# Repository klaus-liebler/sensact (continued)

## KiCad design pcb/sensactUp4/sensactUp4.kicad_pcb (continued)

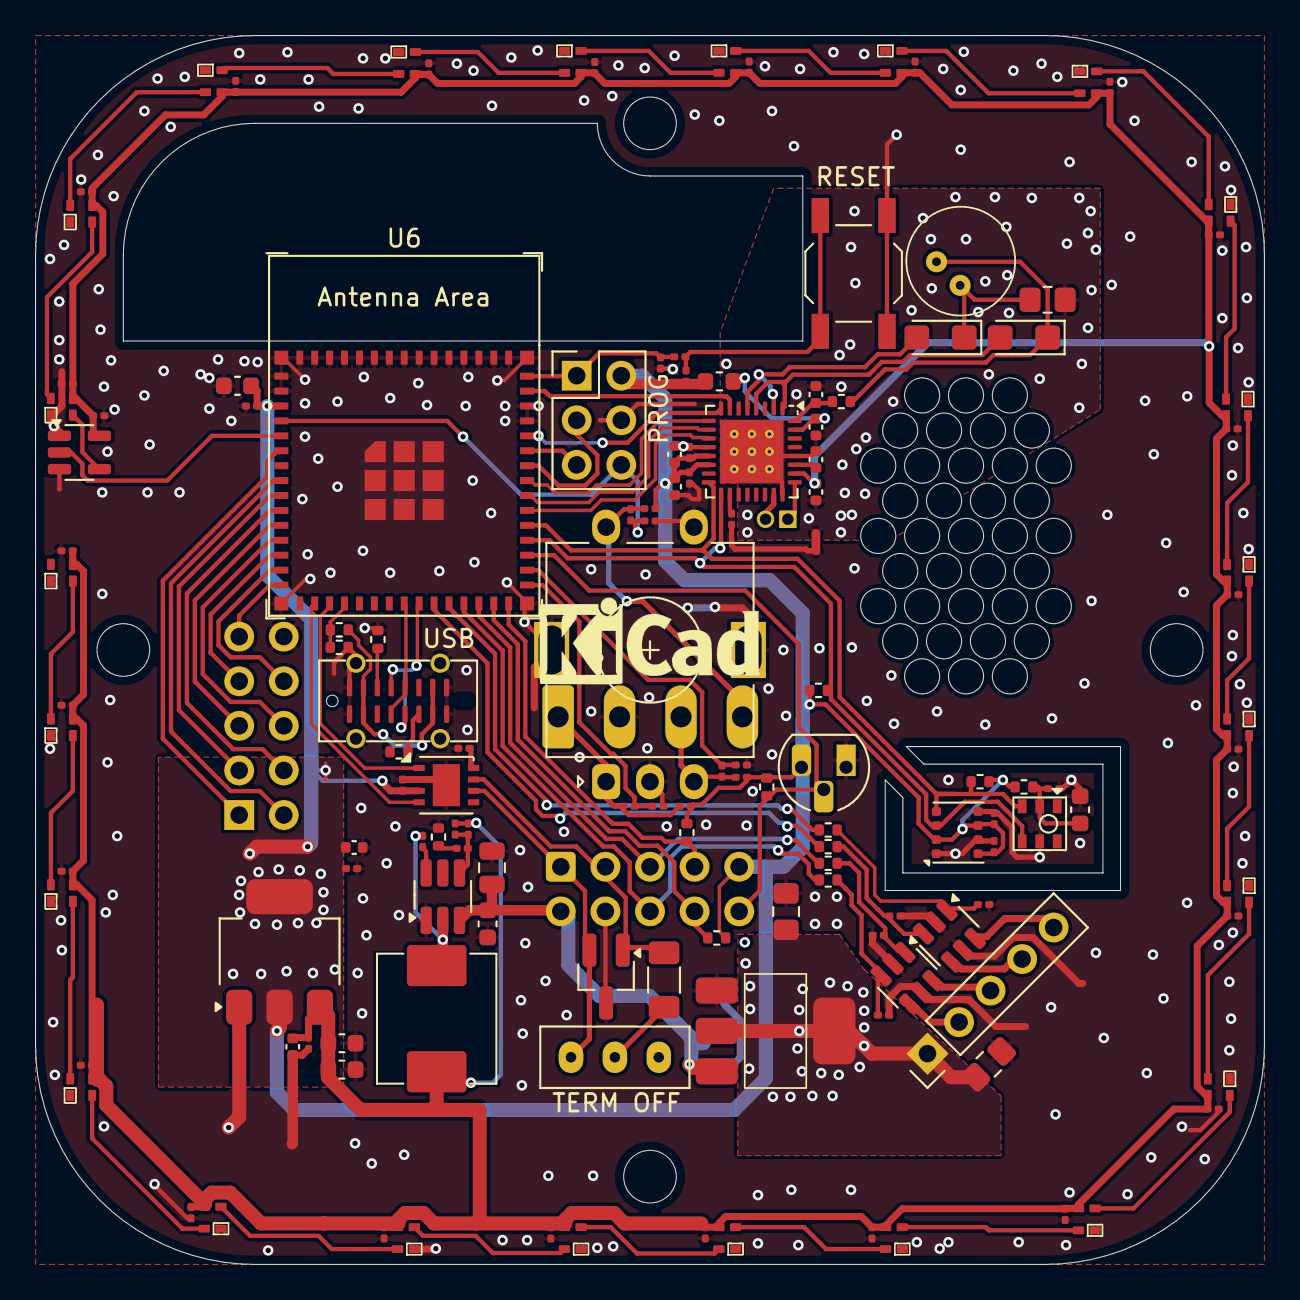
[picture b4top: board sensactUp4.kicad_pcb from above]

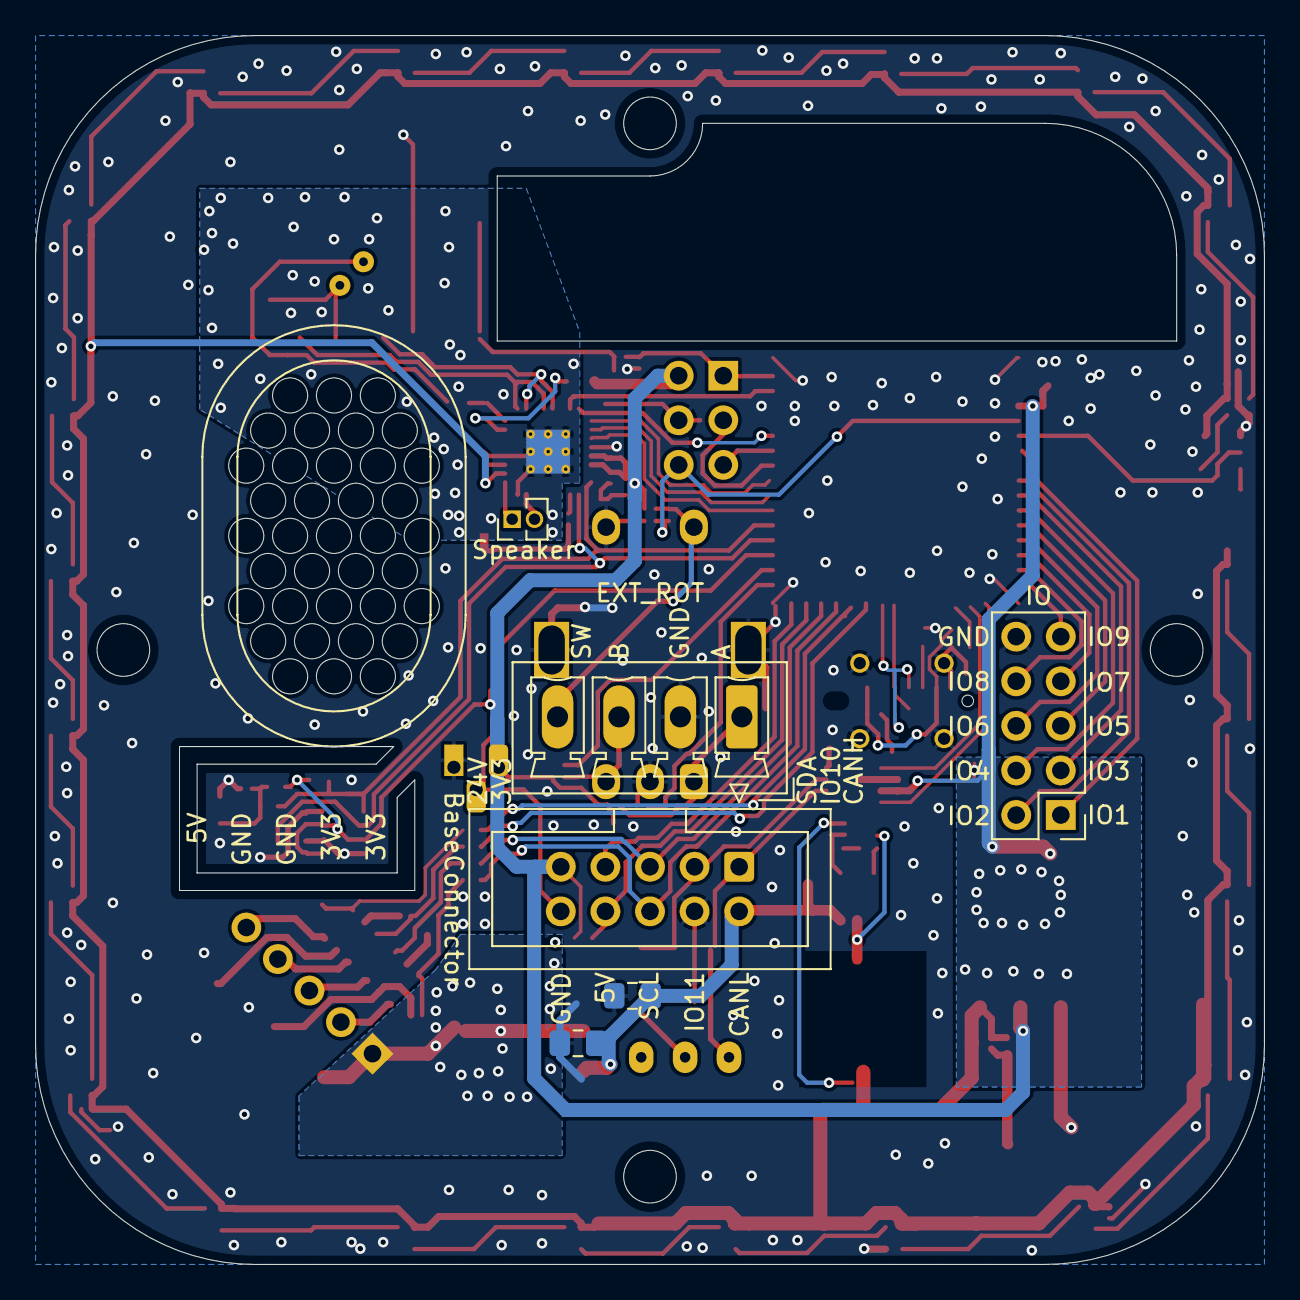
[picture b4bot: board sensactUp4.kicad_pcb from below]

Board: 2 copper layers, 70.0 x 70.0 mm, 147 parts (7 on the bottom side), 99 nets.

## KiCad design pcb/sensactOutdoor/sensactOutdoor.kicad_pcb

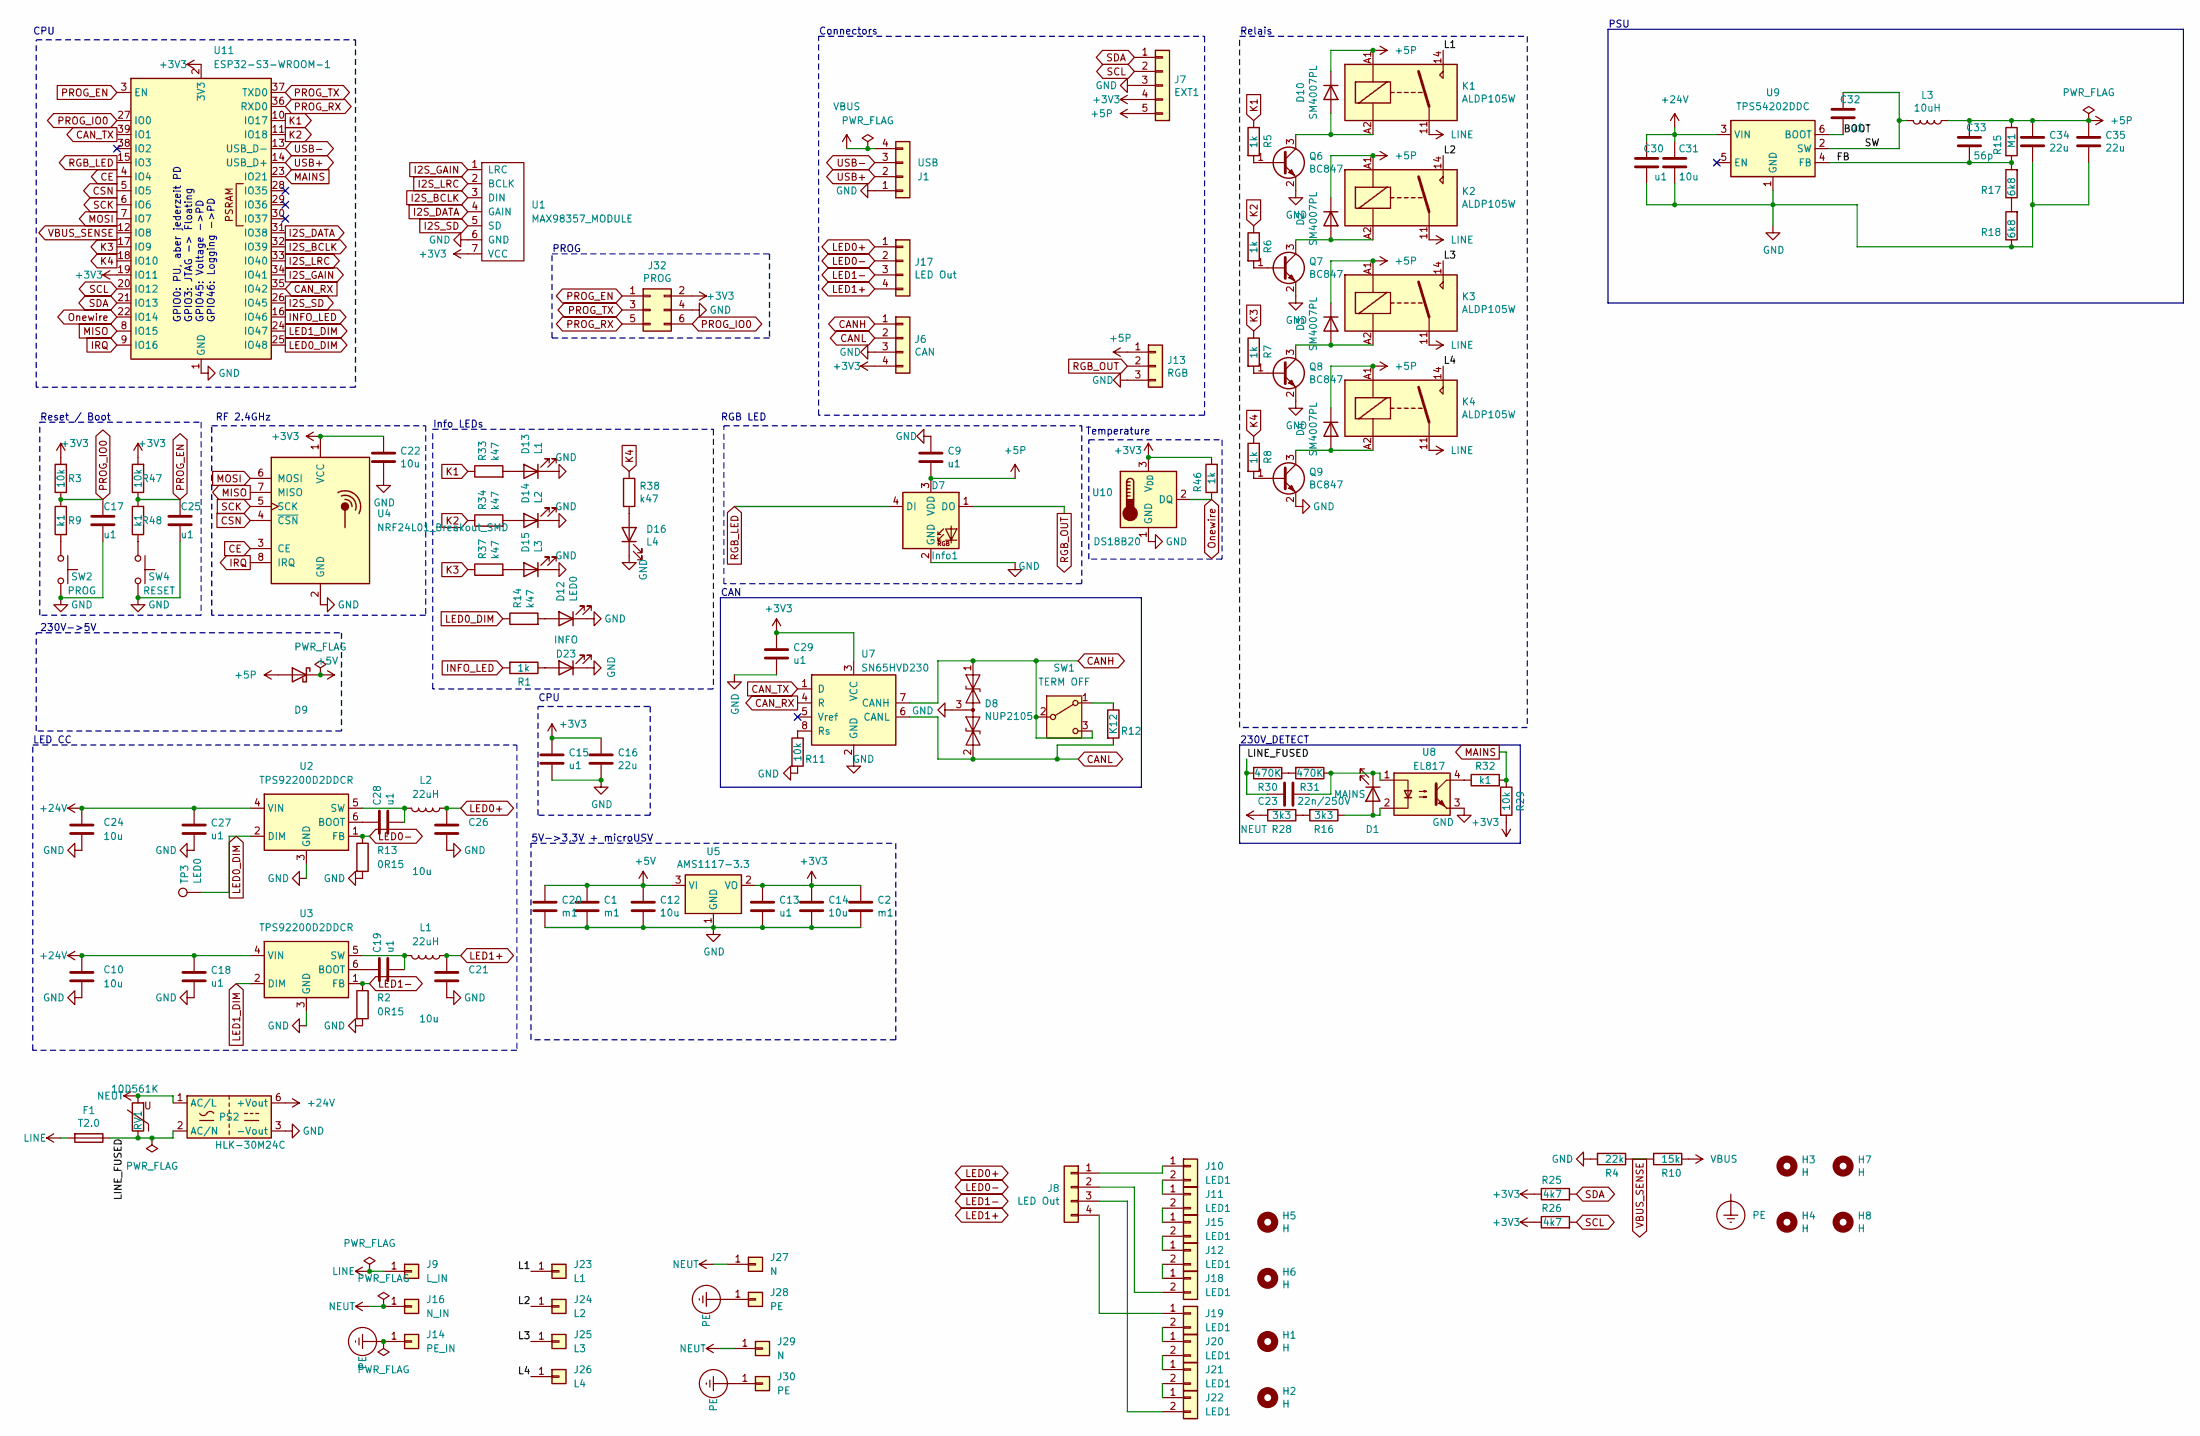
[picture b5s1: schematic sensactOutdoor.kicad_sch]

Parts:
C1, C2, C20: m1; C_1206_3216Metric; JLCPCB C15008
C9, C13, C17, C18, C19, C25, C27, C28, C30, C32: u1; C_0805_2012Metric_Pad1.18x1.45mm_HandSolder
C10, C21, C24, C26, C31: 10u; C_1206_3216Metric_Pad1.33x1.80mm_HandSolder
C12: 10u; C_0805_2012Metric_Pad1.18x1.45mm_HandSolder; JLCPCB C19702
C14, C22: 10u; C_0805_2012Metric_Pad1.18x1.45mm_HandSolder
C15: u1; C_0805_2012Metric_Pad1.18x1.45mm_HandSolder; JLCPCB C1525
C16: 22u; C_0805_2012Metric_Pad1.18x1.45mm_HandSolder; JLCPCB C59461
C23: 22n/250V; C_Rect_L11.0mm_W5.1mm_P10.00mm_MKT
C29: u1; C_0805_2012Metric; MPN GRM033R61A104KE15D
C33: 56p; C_0805_2012Metric_Pad1.18x1.45mm_HandSolder
C34, C35: 22u; C_0805_2012Metric_Pad1.18x1.45mm_HandSolder
D1: MAINS; LED_0805_2012Metric_Pad1.15x1.40mm_HandSolder
D2, D3, D4, D10: SM4007PL; D_SOD-123_handsolder; JLCPCB C64898
D7: Info1; LED_D5.0mm-4_RGB_Staggered_Pins
D8: NUP2105; SOT-23_Handsoldering; MPN NUP2105L
D9: 1N5819WS; D_SMA_Handsoldering
D12: LED0; LED_0805_2012Metric_Pad1.15x1.40mm_HandSolder; JLCPCB C2286
D13: L1; LED_0805_2012Metric_Pad1.15x1.40mm_HandSolder; JLCPCB C2286
D14: L2; LED_0805_2012Metric_Pad1.15x1.40mm_HandSolder; JLCPCB C2286
D15: L3; LED_0805_2012Metric_Pad1.15x1.40mm_HandSolder; JLCPCB C2286
D16: L4; LED_0805_2012Metric_Pad1.15x1.40mm_HandSolder; JLCPCB C2286
D23: INFO; LED_0805_2012Metric_Pad1.15x1.40mm_HandSolder
F1: T2.0; Fuse_Littelfuse_372_D8.50mm
H1, H2, H3, H4, H5, H6, H7, H8: H; MountingHole_3.2mm_M3
J1: USB; PinHeader_1x04_P2.54mm_Vertical
J6: CAN; PhoenixContact_MCV_1,5_4-G-3.5_1x04_P3.50mm_Vertical
J7: EXT1; JST_XH_B5B-XH-A_1x05_P2.50mm_Vertical
J8: LED Out; ÖLFLEX 4x1mm2
J9: L_IN; Flachstecker gewinkelt 4,8 oder 6,35mm
J10, J11, J12, J15, J18, J19, J20, J21, J22: LED1; JST_XH_B2B-XH-A_1x02_P2.50mm_Vertical
J13: RGB; PinHeader_1x03_P2.54mm_Vertical
J14: PE_IN; Flachstecker gewinkelt 4,8 oder 6,35mm
J16: N_IN; Flachstecker gewinkelt 4,8 oder 6,35mm
J17: LED Out; PhoenixContact_MCV_1,5_4-G-3.5_1x04_P3.50mm_Vertical
J23: L1; Flachstecker gewinkelt 4,8 oder 6,35mm
J24: L2; Flachstecker gewinkelt 4,8 oder 6,35mm
J25: L3; Flachstecker gewinkelt 4,8 oder 6,35mm
J26: L4; Flachstecker gewinkelt 4,8 oder 6,35mm
J27, J29: N; Flachstecker gewinkelt 4,8 oder 6,35mm
J28, J30: PE; Flachstecker gewinkelt 4,8 oder 6,35mm
J32: PROG; PinHeader_2x03_P2.54mm_Vertical
K1, K2, K3, K4: ALDP105W; RELAY_ALDP105W
L1, L2: 22uH; L_0630; JLCPCB C408455
L3: 10uH; L_0630
PS2: HLK-30M24C; Converter_ACDC_Hi-Link_HLK-30Mxx
Q6: BC847; SOT-23_Handsoldering; JLCPCB C8512
Q7, Q8, Q9: BC847; SOT-23_Handsoldering
R1, R5, R6, R7, R8, R46: 1k; R_0805_2012Metric_Pad1.20x1.40mm_HandSolder
R2, R13: 0R15; R_1206_3216Metric_Pad1.30x1.75mm_HandSolder; JLCPCB C25271
R3, R29, R47: 10k; R_0805_2012Metric_Pad1.20x1.40mm_HandSolder
R4: 22k; R_0805_2012Metric_Pad1.20x1.40mm_HandSolder
R9, R32, R48: k1; R_0805_2012Metric_Pad1.20x1.40mm_HandSolder
R10: 15k; R_0805_2012Metric_Pad1.20x1.40mm_HandSolder
R11: 10k; R_0805_2012Metric_Pad1.20x1.40mm_HandSolder; MPN 0201WMF1002TEE
R12: K12; R_1206_3216Metric_Pad1.30x1.75mm_HandSolder; MPN 1206W4F1200T5E
R14, R33, R34, R37, R38: k47; R_0805_2012Metric_Pad1.20x1.40mm_HandSolder
R15: M1; R_0805_2012Metric_Pad1.20x1.40mm_HandSolder
R16, R28: 3k3; R_2512_6332Metric_Pad1.40x3.35mm_HandSolder
R17, R18: 6k8; R_0805_2012Metric_Pad1.20x1.40mm_HandSolder
R25, R26: 4k7; R_0805_2012Metric_Pad1.20x1.40mm_HandSolder
R30, R31: 470K; R_2512_6332Metric_Pad1.40x3.35mm_HandSolder
RV1: 10D561K; RV_Disc_D12mm_W3.9mm_P7.5mm
SW1: TERM OFF; Switch_SS12D00
SW2: PROG; SW_SPST_TL3342_smaller_handsolder
SW4: RESET; SW_SPST_TL3342_smaller_handsolder
TP3: LED0; TestPoint_THTPad_D2.0mm_Drill1.0mm
U1: MAX98357_MODULE; PinHeader_1x07_P2.54mm_Vertical
U2, U3: TPS92200D2DDCR; SOT-23-6_Handsoldering
U4: NRF24L01_Breakout_SMD; NRF24L01-Module-SMD
U5: AMS1117-3.3; SOT-223-3_TabPin2_HANDSOLDER
U7: SN65HVD230; SOIC-8_3.9x4.9mm_Pitch1.27mm_handsolder; MPN SN65HVD230DR
U8: EL817; SO-4_7.6x3.6mm_P2.54mm_handsolder
U9: TPS54202DDC; SOT-23-6_Handsoldering
U10: DS18B20; TO-92L_HandSolder
U11: ESP32-S3-WROOM-1; ESP32-S3-WROOM-1_handsolder

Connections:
+3V3: C2.1, C13.1, C14.1, C15.1, C16.1, C22.1, C29.1, J6.4, J7.4, J32.2, R3.2, R25.1, R26.1, R29.2, R46.2, R47.2, U1.7 (VCC), U4.1 (VCC), U5.2 (VO), U7.3 (VCC), U10.3 (V_{DD}), U11.2 (3V3), U11.19 (IO11)
+5P: C9.2, C33.2, C34.1, C35.1, D2.1 (K), D3.1 (K), D4.1 (K), D7.3 (VDD), D9.2 (A), D10.1 (K), J7.5, J13.1, K1.A1, K2.A1, K3.A1, K4.A1, L3.1, R15.1
+5V: C1.1, C12.1, C20.1, D9.1 (K), U5.3 (VI)
+24V: C10.1, C18.1, C24.1, C27.1, C30.2, C31.2, PS2.6 (+Vout), U2.4 (VIN), U3.4 (VIN), U9.3 (VIN)
/BOOT: C32.1, U9.6 (BOOT)
/FB: C33.1, R15.2, R17.2, U9.4 (FB)
/L1: J23.1, K1.14
/L2: J24.1, K2.14
/L3: J25.1, K3.14
/L4: J26.1, K4.14
/LINE_FUSED: C23.1, F1.1, PS2.2 (AC/N), R30.2, RV1.1
/SW: C32.2, L3.2, U9.2 (SW)
CANH: D8.1 (A1), J6.1, SW1.2 (B), SW1.3 (C), U7.7 (CANH)
CANL: D8.2 (A2), J6.2, R12.2, U7.6 (CANL)
CAN_RX: U7.4 (R), U11.35 (IO42)
CAN_TX: U7.1 (D), U11.39 (IO1)
CE: U4.3 (CE), U11.4 (IO4)
CSN: U4.4 (~CSN), U11.5 (IO5)
GND: C1.2, C2.2, C9.1, C10.2, C12.2, C13.2, C14.2, C15.2, C16.2, C17.2, C18.2, C20.2, C21.2, C22.2, C24.2, C25.2, C26.2, C27.2, C29.2, C30.1, C31.1, C34.2, C35.2, D7.2 (GND), D8.3 (common), D12.1 (K), D13.1 (K), D14.1 (K), D15.1 (K), D16.1 (K), D23.1 (K), J1.1, J6.3, J7.3, J13.3, J32.4, PS2.3 (-Vout), Q6.2 (E), Q7.2 (E), Q8.2 (E), Q9.2 (E), R2.2, R4.2, R11.2, R13.2, R18.1, SW2.2, SW4.2, U1.6 (GND), U2.3 (GND), U3.3 (GND), U4.2 (GND), U5.1 (GND), U7.2 (GND), U8.3, U9.1 (GND), U10.1 (GND), U11.1 (GND), U11.40 (GND), U11.41 (GND)
I2S_BCLK: U1.3 (DIN), U11.32 (IO39)
I2S_DATA: U1.4 (GAIN), U11.31 (IO38)
I2S_GAIN: U1.1 (LRC), U11.34 (IO41)
I2S_LRC: U1.2 (BCLK), U11.33 (IO40)
I2S_SD: U1.5 (SD), U11.26 (IO45)
INFO_LED: R1.2, U11.16 (IO46)
IRQ: U4.8 (IRQ), U11.9 (IO16)
K1: R5.1, R33.1, U11.10 (IO17)
K2: R6.1, R34.1, U11.11 (IO18)
K3: R7.1, R37.1, U11.17 (IO9)
K4: R8.1, R38.1, U11.18 (IO10)
LED0+: C26.1, J17.1, L2.1
LED0-: J17.2, R13.1, U2.1 (FB)
LED0_DIM: R14.1, TP3.1, U2.2 (DIM), U11.25 (IO48)
LED1+: C21.1, J17.4, L1.1
LED1-: J17.3, R2.1, U3.1 (FB)
LED1_DIM: U3.2 (DIM), U11.24 (IO47)
LINE: F1.2, J9.1, K1.11, K2.11, K3.11, K4.11
MAINS: R29.1, R32.2, U11.23 (IO21)
MISO: U4.7 (MISO), U11.8 (IO15)
MOSI: U4.6 (MOSI), U11.7 (IO7)
NEUT: J16.1, J27.1, J29.1, PS2.1 (AC/L), R28.2, RV1.2
unnamed: D1.2 (A), R16.1, U8.2
unnamed: C23.2, D1.1 (K), R31.1, U8.1
unnamed: D2.2 (A), K2.A2, Q7.3 (C)
unnamed: D3.2 (A), K3.A2, Q8.3 (C)
unnamed: D4.2 (A), K4.A2, Q9.3 (C)
unnamed: D10.2 (A), K1.A2, Q6.3 (C)
unnamed: D12.2 (A), R14.2
unnamed: D13.2 (A), R33.2
unnamed: D14.2 (A), R34.2
unnamed: D15.2 (A), R37.2
unnamed: D16.2 (A), R38.2
unnamed: D23.2 (A), R1.1
unnamed: J8.1, J10.1
unnamed: J10.2, J11.1
unnamed: J11.2, J15.1
unnamed: J12.1, J15.2
unnamed: J12.2, J18.1
unnamed: J8.2, J18.2
unnamed: J8.4, J19.1
unnamed: J19.2, J20.1
unnamed: J20.2, J21.1
unnamed: J21.2, J22.1
unnamed: J8.3, J22.2
unnamed: Q6.1 (B), R5.2
unnamed: Q7.1 (B), R6.2
unnamed: Q8.1 (B), R7.2
unnamed: Q9.1 (B), R8.2
unnamed: R9.1, SW2.1
unnamed: R16.2, R28.1
unnamed: R17.1, R18.2
unnamed: R30.1, R31.2
unnamed: R32.1, U8.4
unnamed: R48.1, SW4.1
unnamed: R12.1, SW1.1 (A)
unnamed: C28.1, U2.6 (BOOT)
unnamed: C28.2, L2.2, U2.5 (SW)
unnamed: C19.1, U3.6 (BOOT)
unnamed: C19.2, L1.2, U3.5 (SW)
unnamed: R11.1, U7.8 (Rs)
Onewire: R46.1, U10.2 (DQ), U11.22 (IO14)
PE: J14.1, J28.1, J30.1
PROG_EN: C25.1, J32.1, R47.1, R48.2, U11.3 (EN)
PROG_IO0: C17.1, J32.6, R3.1, R9.2, U11.27 (IO0)
PROG_RX: J32.5, U11.36 (RXD0)
PROG_TX: J32.3, U11.37 (TXD0)
RGB_LED: D7.4 (DI), U11.15 (IO3)
RGB_OUT: D7.1 (DO), J13.2
SCK: U4.5 (SCK), U11.6 (IO6)
SCL: J7.2, R26.2, U11.20 (IO12)
SDA: J7.1, R25.2, U11.21 (IO13)
USB+: J1.2, U11.14 (USB_D+)
USB-: J1.3, U11.13 (USB_D-)
VBUS: J1.4, R10.1
VBUS_SENSE: R4.1, R10.2, U11.12 (IO8)

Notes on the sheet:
230V->5V
Relais
CPU
Temperature
LED CC
PSU
RF 2.4GHz
Connectors
CAN
230V_DETECT
Info LEDs
Reset / Boot
RGB LED
PROG
5V->3,3V + microUSV
GPIO0: PU, aber jederzeit PD GPIO3: JTAG -> Floating GPIO45: Voltage ->PD GPIO46: Logging ->PD

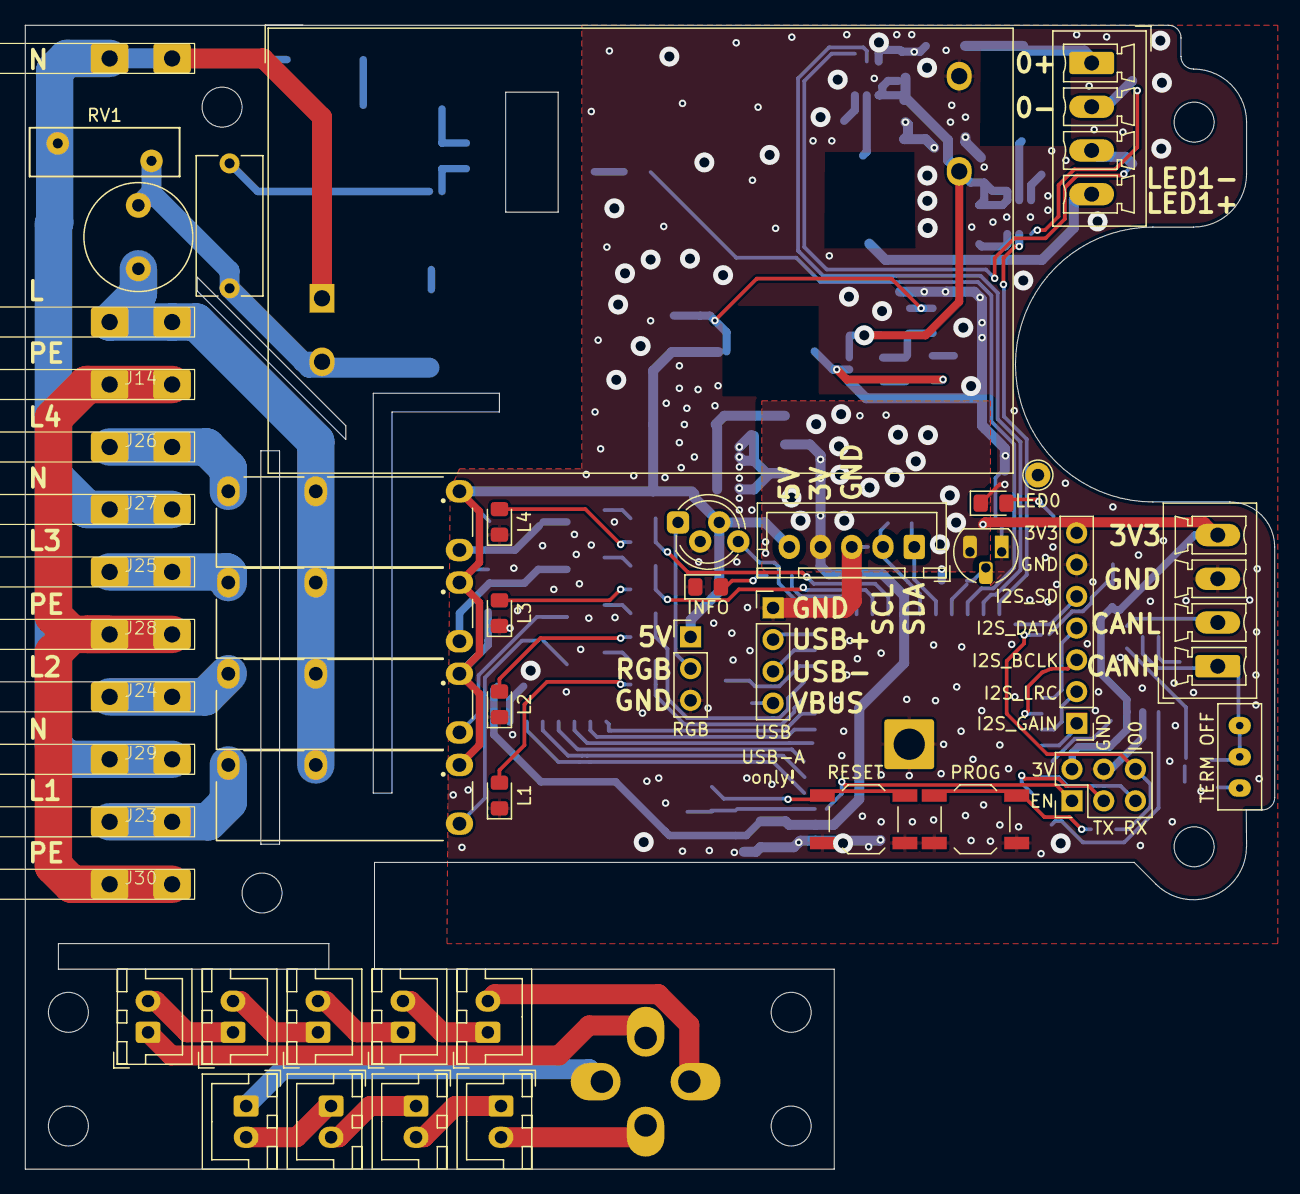
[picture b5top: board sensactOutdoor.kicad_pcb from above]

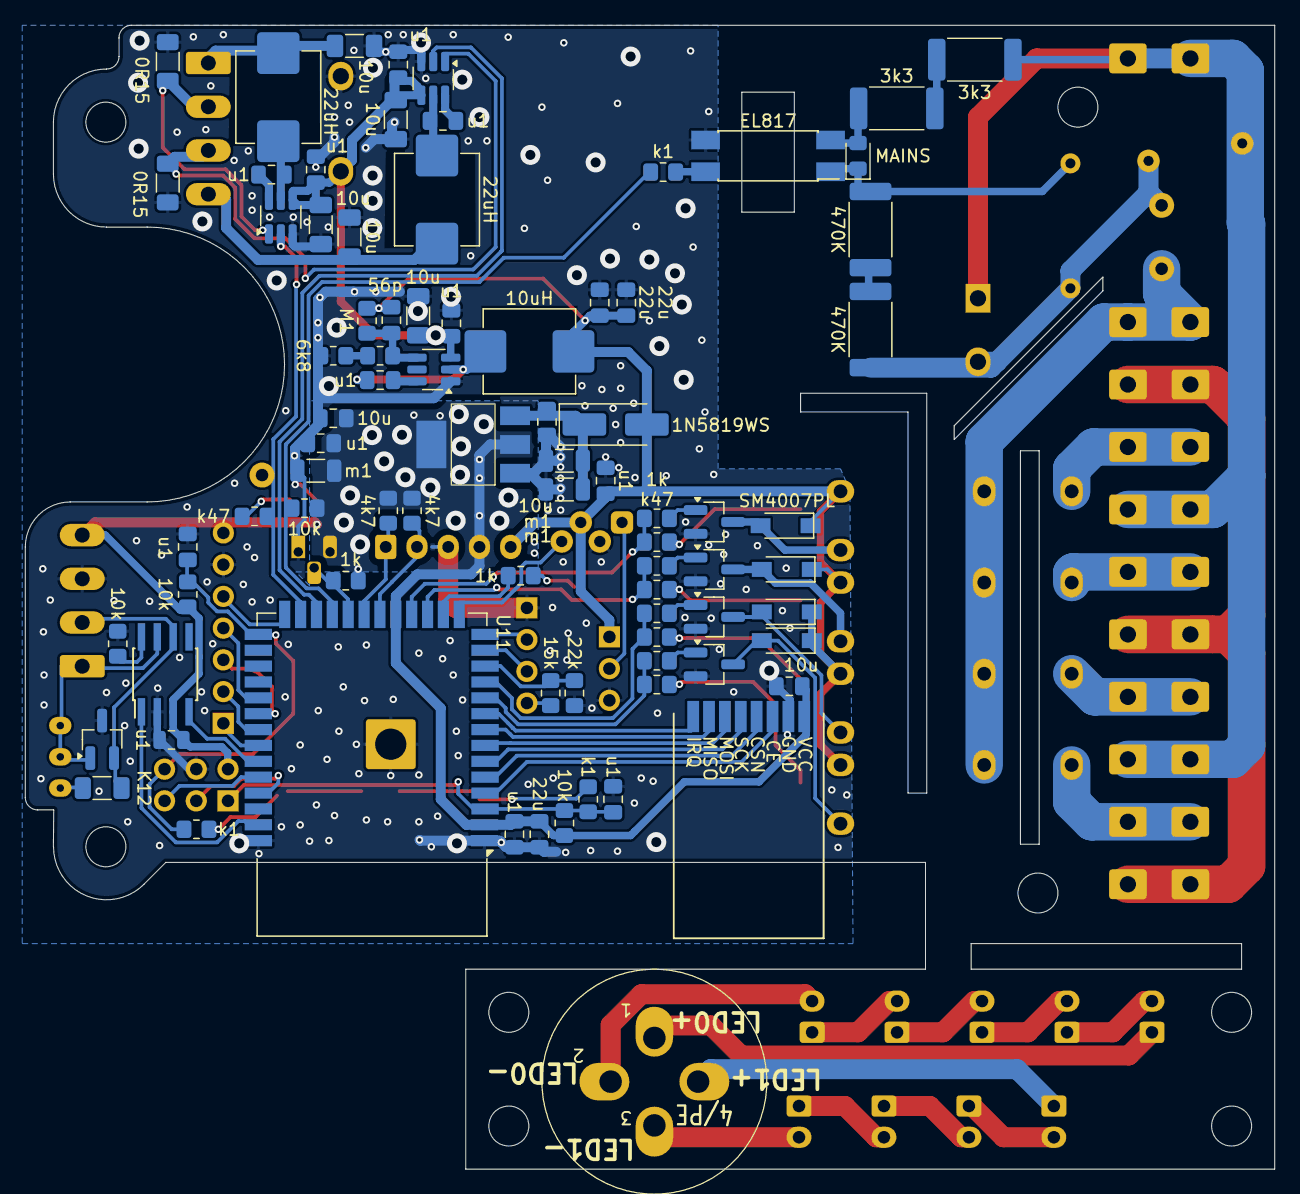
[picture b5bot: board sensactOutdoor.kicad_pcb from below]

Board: 2 copper layers, 100.0 x 91.6 mm, 137 parts (82 on the bottom side), 95 nets.

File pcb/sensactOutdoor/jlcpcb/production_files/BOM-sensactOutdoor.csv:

Comment,Designator,Footprint,LCSC,Quantity
m1,"C1,C2,C20",C_1206_3216Metric,C15008,3
u1,C15,C_0805_2012Metric_Pad1.18x1.45mm_HandSolder,C1525,1
10u,C12,C_0805_2012Metric_Pad1.18x1.45mm_HandSolder,C19702,1
LED0,"D12,D13,D14,D15,D16",LED_0805_2012Metric_Pad1.15x1.40mm_HandSolder,C2286,5
0R15,"R13,R2",R_1206_3216Metric_Pad1.30x1.75mm_HandSolder,C25271,2
22uH,"L1,L2",L_0630,C408455,2
u1,"C13,C17,C18,C19,C25,C27,C28,C30,C32,C9",C_0805_2012Metric_Pad1.18x1.45mm_HandSolder,C49678,10
22u,C16,C_0805_2012Metric_Pad1.18x1.45mm_HandSolder,C59461,1
SM4007PL,"D10,D2,D3,D4",D_SOD-123_handsolder,C64898,4
BC847,Q6,SOT-23_Handsoldering,C8512,1
LED1,J22,JST_XH_B2B-XH-A_1x02_P2.50mm_Vertical,,1
H,H6,MountingHole_3.2mm_M3,,1
L1,J23,"Flachstecker gewinkelt 4,8 oder 6,35mm",,1
LED1,J15,JST_XH_B2B-XH-A_1x02_P2.50mm_Vertical,,1
ALDP105W,K1,RELAY_ALDP105W,,1
H,H1,MountingHole_3.2mm_M3,,1
LED1,J10,JST_XH_B2B-XH-A_1x02_P2.50mm_Vertical,,1
N,J29,"Flachstecker gewinkelt 4,8 oder 6,35mm",,1
LED Out,J17,"PhoenixContact_MCV_1,5_4-G-3.5_1x04_P3.50mm_Vertical",,1
H,H5,MountingHole_3.2mm_M3,,1
INFO,D23,LED_0805_2012Metric_Pad1.15x1.40mm_HandSolder,,1
RGB,J13,PinHeader_1x03_P2.54mm_Vertical,,1
DS18B20,U10,TO-92L_HandSolder,,1
LED1,J19,JST_XH_B2B-XH-A_1x02_P2.50mm_Vertical,,1
LED0,TP3,TestPoint_THTPad_D2.0mm_Drill1.0mm,,1
10D561K,RV1,RV_Disc_D12mm_W3.9mm_P7.5mm,,1
N,J27,"Flachstecker gewinkelt 4,8 oder 6,35mm",,1
L_IN,J9,"Flachstecker gewinkelt 4,8 oder 6,35mm",,1
T2.0,F1,Fuse_Littelfuse_372_D8.50mm,,1
MAX98357_MODULE,U1,PinHeader_1x07_P2.54mm_Vertical,,1
LED1,J12,JST_XH_B2B-XH-A_1x02_P2.50mm_Vertical,,1
PE,J28,"Flachstecker gewinkelt 4,8 oder 6,35mm",,1
H,H8,MountingHole_3.2mm_M3,,1
L3,J25,"Flachstecker gewinkelt 4,8 oder 6,35mm",,1
ALDP105W,K2,RELAY_ALDP105W,,1
N_IN,J16,"Flachstecker gewinkelt 4,8 oder 6,35mm",,1
LED1,J11,JST_XH_B2B-XH-A_1x02_P2.50mm_Vertical,,1
PROG,SW2,SW_SPST_TL3342_smaller_handsolder,,1
LED1,J20,JST_XH_B2B-XH-A_1x02_P2.50mm_Vertical,,1
USB,J1,PinHeader_1x04_P2.54mm_Vertical,,1
22n/250V,C23,C_Rect_L11.0mm_W5.1mm_P10.00mm_MKT,,1
H,H3,MountingHole_3.2mm_M3,,1
TERM OFF,SW1,Switch_SS12D00,,1
PROG,J32,PinHeader_2x03_P2.54mm_Vertical,,1
ALDP105W,K4,RELAY_ALDP105W,,1
RESET,SW4,SW_SPST_TL3342_smaller_handsolder,,1
L4,J26,"Flachstecker gewinkelt 4,8 oder 6,35mm",,1
HLK-30M24C,PS2,Converter_ACDC_Hi-Link_HLK-30Mxx,,1
LED1,J18,JST_XH_B2B-XH-A_1x02_P2.50mm_Vertical,,1
PE,J30,"Flachstecker gewinkelt 4,8 oder 6,35mm",,1
H,H2,MountingHole_3.2mm_M3,,1
ALDP105W,K3,RELAY_ALDP105W,,1
Info1,D7,LED_D5.0mm-4_RGB_Staggered_Pins,,1
LED1,J21,JST_XH_B2B-XH-A_1x02_P2.50mm_Vertical,,1
H,H4,MountingHole_3.2mm_M3,,1
PE_IN,J14,"Flachstecker gewinkelt 4,8 oder 6,35mm",,1
EXT1,J7,JST_XH_B5B-XH-A_1x05_P2.50mm_Vertical,,1
L2,J24,"Flachstecker gewinkelt 4,8 oder 6,35mm",,1
CAN,J6,"PhoenixContact_MCV_1,5_4-G-3.5_1x04_P3.50mm_Vertical",,1
H,H7,MountingHole_3.2mm_M3,,1
1k,R7,R_0805_2012Metric_Pad1.20x1.40mm_HandSolder,,1
MAINS,D1,LED_0805_2012Metric_Pad1.15x1.40mm_HandSolder,,1
LED Out,J8,ÖLFLEX 4x1mm2,,1
AMS1117-3.3,U5,SOT-223-3_TabPin2_HANDSOLDER,,1
470K,R31,R_2512_6332Metric_Pad1.40x3.35mm_HandSolder,,1
1k,R1,R_0805_2012Metric_Pad1.20x1.40mm_HandSolder,,1
3k3,R16,R_2512_6332Metric_Pad1.40x3.35mm_HandSolder,,1
470K,R30,R_2512_6332Metric_Pad1.40x3.35mm_HandSolder,,1
15k,R10,R_0805_2012Metric_Pad1.20x1.40mm_HandSolder,,1
10u,C21,C_1206_3216Metric_Pad1.33x1.80mm_HandSolder,,1
k1,R32,R_0805_2012Metric_Pad1.20x1.40mm_HandSolder,,1
NUP2105,D8,SOT-23_Handsoldering,,1
BC847,Q7,SOT-23_Handsoldering,,1
BC847,Q9,SOT-23_Handsoldering,,1
K12,R12,R_1206_3216Metric_Pad1.30x1.75mm_HandSolder,,1
10uH,L3,L_0630,,1
10u,C22,C_0805_2012Metric_Pad1.18x1.45mm_HandSolder,,1
10u,C31,C_1206_3216Metric_Pad1.33x1.80mm_HandSolder,,1
TPS92200D2DDCR,U2,SOT-23-6_Handsoldering,,1
1k,R8,R_0805_2012Metric_Pad1.20x1.40mm_HandSolder,,1
4k7,R25,R_0805_2012Metric_Pad1.20x1.40mm_HandSolder,,1
6k8,R17,R_0805_2012Metric_Pad1.20x1.40mm_HandSolder,,1
10k,R3,R_0805_2012Metric_Pad1.20x1.40mm_HandSolder,,1
TPS54202DDC,U9,SOT-23-6_Handsoldering,,1
TPS92200D2DDCR,U3,SOT-23-6_Handsoldering,,1
k47,R38,R_0805_2012Metric_Pad1.20x1.40mm_HandSolder,,1
3k3,R28,R_2512_6332Metric_Pad1.40x3.35mm_HandSolder,,1
10u,C24,C_1206_3216Metric_Pad1.33x1.80mm_HandSolder,,1
k47,R34,R_0805_2012Metric_Pad1.20x1.40mm_HandSolder,,1
1N5819WS,D9,D_SMA_Handsoldering,,1
10k,R47,R_0805_2012Metric_Pad1.20x1.40mm_HandSolder,,1
k47,R33,R_0805_2012Metric_Pad1.20x1.40mm_HandSolder,,1
10k,R11,R_0805_2012Metric_Pad1.20x1.40mm_HandSolder,,1
k1,R9,R_0805_2012Metric_Pad1.20x1.40mm_HandSolder,,1
10u,C26,C_1206_3216Metric_Pad1.33x1.80mm_HandSolder,,1
k1,R48,R_0805_2012Metric_Pad1.20x1.40mm_HandSolder,,1
SN65HVD230,U7,SOIC-8_3.9x4.9mm_Pitch1.27mm_handsolder,,1
10u,C14,C_0805_2012Metric_Pad1.18x1.45mm_HandSolder,,1
22u,C34,C_0805_2012Metric_Pad1.18x1.45mm_HandSolder,,1
4k7,R26,R_0805_2012Metric_Pad1.20x1.40mm_HandSolder,,1
10k,R29,R_0805_2012Metric_Pad1.20x1.40mm_HandSolder,,1
22u,C35,C_0805_2012Metric_Pad1.18x1.45mm_HandSolder,,1
22k,R4,R_0805_2012Metric_Pad1.20x1.40mm_HandSolder,,1
k47,R14,R_0805_2012Metric_Pad1.20x1.40mm_HandSolder,,1
BC847,Q8,SOT-23_Handsoldering,,1
10u,C10,C_1206_3216Metric_Pad1.33x1.80mm_HandSolder,,1
EL817,U8,SO-4_7.6x3.6mm_P2.54mm_handsolder,,1
M1,R15,R_0805_2012Metric_Pad1.20x1.40mm_HandSolder,,1
1k,R5,R_0805_2012Metric_Pad1.20x1.40mm_HandSolder,,1
1k,R6,R_0805_2012Metric_Pad1.20x1.40mm_HandSolder,,1
56p,C33,C_0805_2012Metric_Pad1.18x1.45mm_HandSolder,,1
6k8,R18,R_0805_2012Metric_Pad1.20x1.40mm_HandSolder,,1
1k,R46,R_0805_2012Metric_Pad1.20x1.40mm_HandSolder,,1
u1,C29,C_0805_2012Metric,,1
ESP32-S3-WROOM-1,U11,ESP32-S3-WROOM-1_handsolder,,1
k47,R37,R_0805_2012Metric_Pad1.20x1.40mm_HandSolder,,1
NRF24L01_Breakout_SMD,U4,NRF24L01-Module-SMD,,1

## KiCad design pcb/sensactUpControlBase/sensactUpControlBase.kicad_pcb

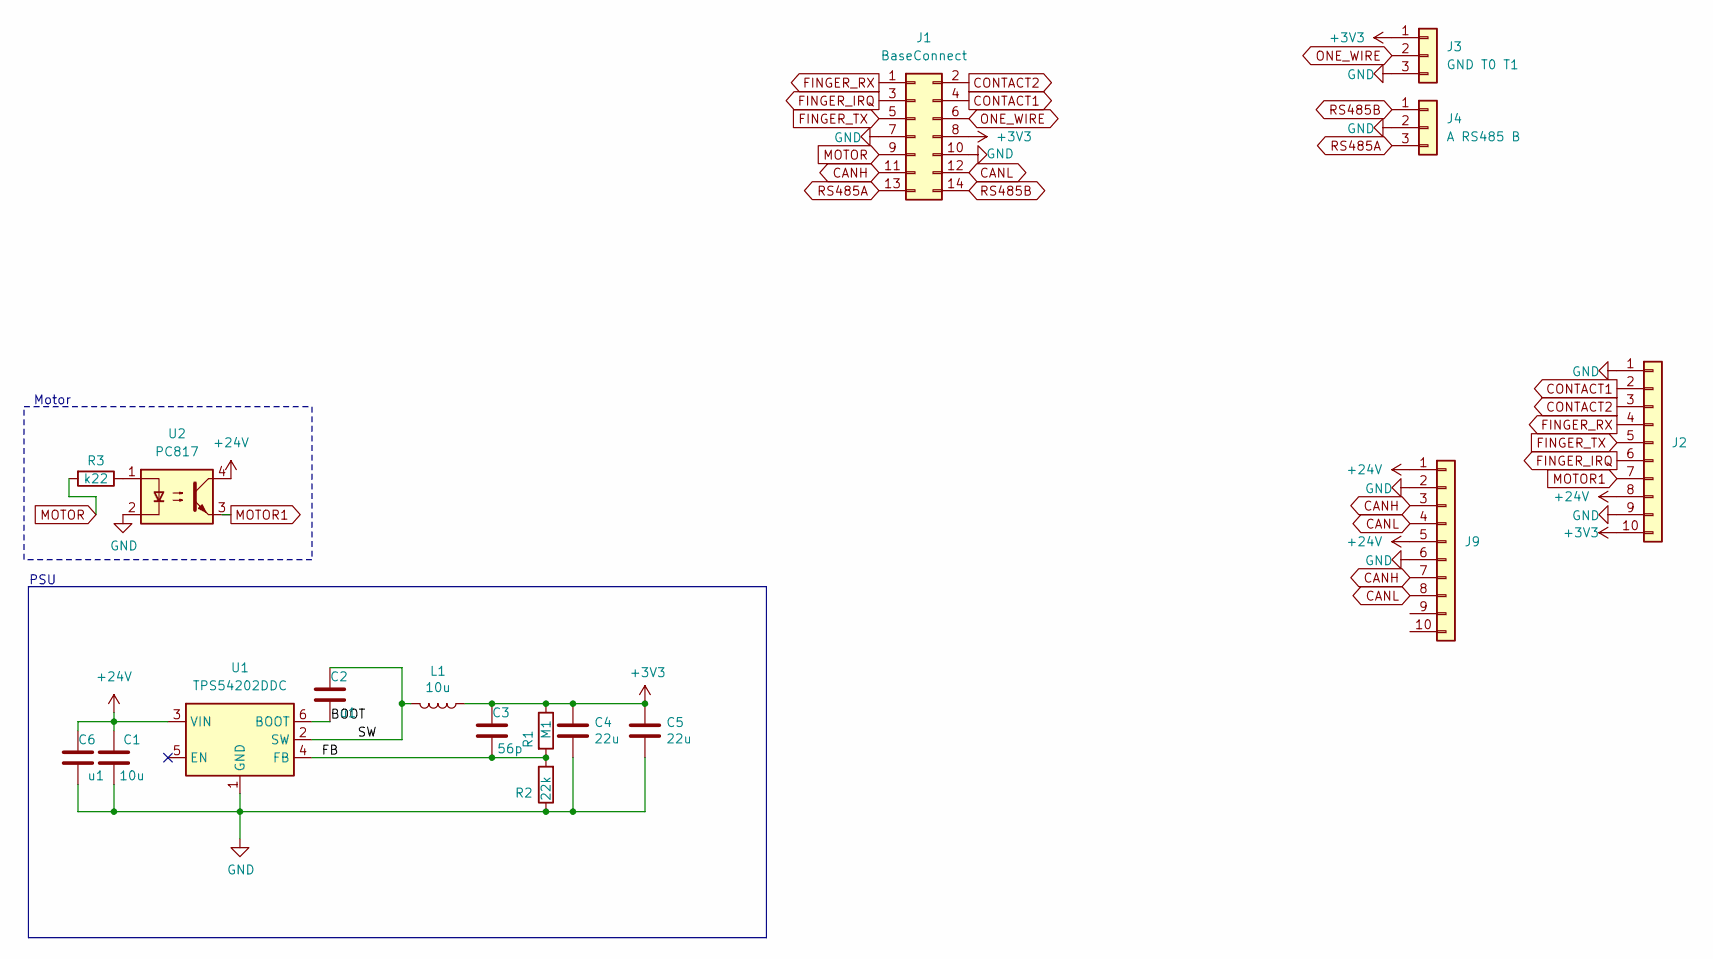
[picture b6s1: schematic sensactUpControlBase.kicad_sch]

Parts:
C1: 10u; C_1206_3216Metric_Pad1.33x1.80mm_HandSolder
C2, C6: u1; C_0805_2012Metric_Pad1.18x1.45mm_HandSolder
C3: 56p; C_0805_2012Metric_Pad1.18x1.45mm_HandSolder
C4, C5: 22u; C_0805_2012Metric_Pad1.18x1.45mm_HandSolder
J1: BaseConnect; PinHeader_2x07_P2.54mm_Vertical
J2, J9: WAGO_250-210
J3: GND T0 T1; WAGO_250_203A
J4: A RS485 B; WAGO_250_203A
L1: 10u; L_0630
R1: M1; R_0805_2012Metric_Pad1.20x1.40mm_HandSolder
R2: 22k; R_0805_2012Metric_Pad1.20x1.40mm_HandSolder
R3: k22; R_0805_2012Metric_Pad1.20x1.40mm_HandSolder
U1: TPS54202DDC; SOT-23-6_Handsoldering
U2: PC817; mdip_4_handsolder

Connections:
+3V3: C3.2, C4.1, C5.1, J1.8, J2.10, J3.1, L1.1, R1.1
+24V: C1.2, C6.2, J2.8, J9.1, J9.5, U1.3 (VIN), U2.4
/BOOT: C2.1, U1.6 (BOOT)
/FB: C3.1, R1.2, R2.2, U1.4 (FB)
/SW: C2.2, L1.2, U1.2 (SW)
CANH: J1.11, J9.3, J9.7
CANL: J1.12, J9.4, J9.8
CONTACT1: J1.4, J2.2
CONTACT2: J1.2, J2.3
FINGER_IRQ: J1.3, J2.6
FINGER_RX: J1.1, J2.4
FINGER_TX: J1.5, J2.5
GND: C1.1, C4.2, C5.2, C6.1, J1.7, J1.10, J2.1, J2.9, J3.3, J4.2, J9.2, J9.6, R2.1, U1.1 (GND), U2.2
MOTOR: J1.9, R3.2
MOTOR1: J2.7, U2.3
unnamed: R3.1, U2.1
ONE_WIRE: J1.6, J3.2
RS485A: J1.13, J4.3
RS485B: J1.14, J4.1

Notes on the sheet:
Motor
PSU

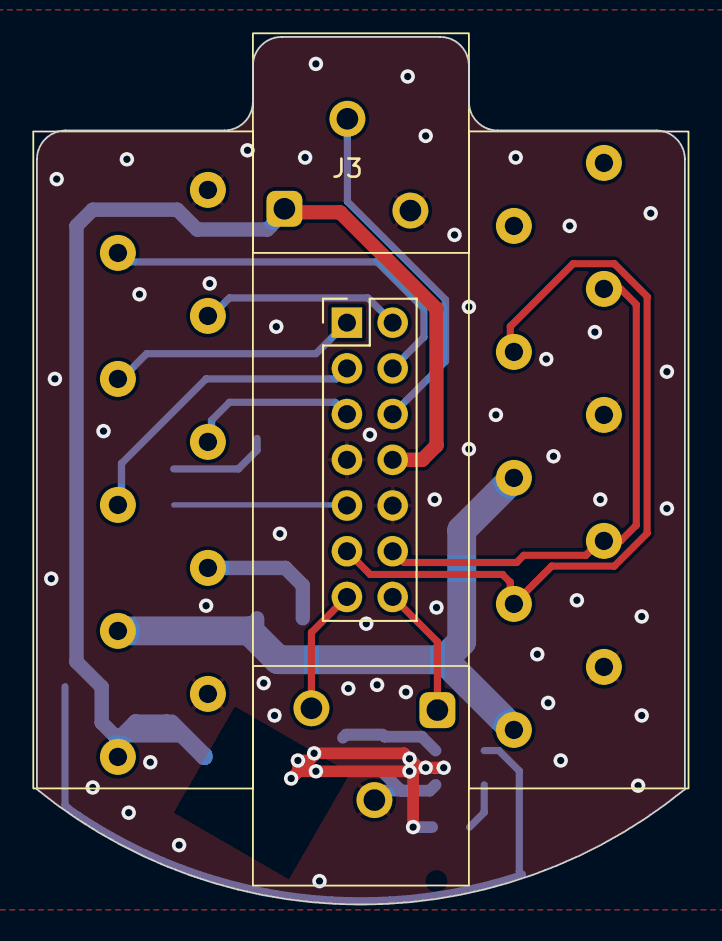
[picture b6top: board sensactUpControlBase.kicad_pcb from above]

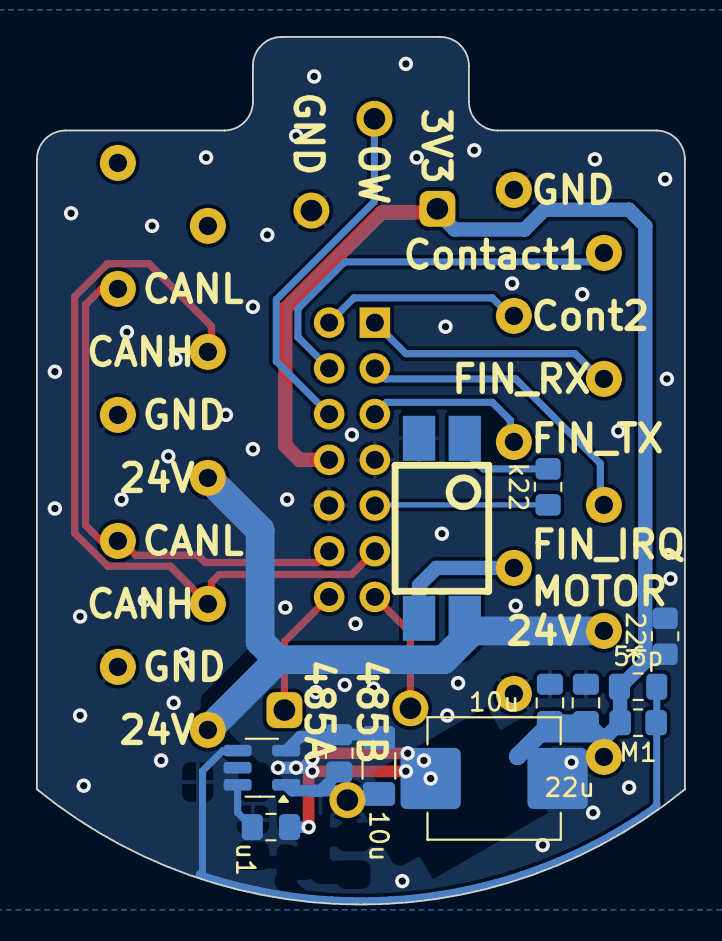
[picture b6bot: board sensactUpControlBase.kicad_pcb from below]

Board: 2 copper layers, 36.0 x 48.2 mm, 17 parts (12 on the bottom side), 19 nets.

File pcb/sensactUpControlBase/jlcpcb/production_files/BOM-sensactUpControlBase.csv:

Comment,Designator,Footprint,LCSC
10u,L1,L_0630,
GND T0 T1,J3,KF250-3.5-3P-A,
BaseConnect,J1,PinHeader_2x07_P2.54mm_Vertical,
~,J9,WAGO_250-210,
A RS485 B,J4,KF250-3.5-3P-A,
~,J2,WAGO_250-210,
22u,C4,C_0805_2012Metric_Pad1.18x1.45mm_HandSolder,
10u,C1,C_1206_3216Metric_Pad1.33x1.80mm_HandSolder,
56p,C3,C_0805_2012Metric_Pad1.18x1.45mm_HandSolder,
u1,C2,C_0805_2012Metric_Pad1.18x1.45mm_HandSolder,
PC817,U2,mdip_4_handsolder,
22u,C5,C_0805_2012Metric_Pad1.18x1.45mm_HandSolder,
22k,R2,R_0805_2012Metric_Pad1.20x1.40mm_HandSolder,
M1,R1,R_0805_2012Metric_Pad1.20x1.40mm_HandSolder,
k22,R3,R_0805_2012Metric_Pad1.20x1.40mm_HandSolder,
TPS54202DDC,U1,SOT-23-6_Handsoldering,
